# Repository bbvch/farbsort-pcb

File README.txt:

Eagle design files for Farbsort Cape for Beagle Bone

My work was based on Adafruit's Proto Cape Kit for Beagle Bone. See details below.

Adafruit Proto Cape Kit for Beagle Bone

These are the Eagle CAD files for the Adafruit Proto Cape Kit for Beagle Bone:
  ----> http://www.adafruit.com/products/572

Adafruit invests time and resources providing this open source design, please support Adafruit and open-source hardware by purchasing products from Adafruit!

Add some circuitry to your Beagle Bone with our lovely Proto Cape. If you have a 'Bone you need one of these! This PCB fits neatly on top of a Beagle Bone, without getting in the way of the Ethernet jack, and provides a breakout to both 46 pin headers - with individual numbering to keep them straight. We also threw down some strips to access the 5V and 3V power supplies as well as two SMT breakouts, one for SOIC-8's and one for SOT-23's.

Kit comes with a double-sided FR4 PCB and 3 sticks of header. You'll need to place the header into the Beagle Bone and then solder the Proto Cape PCB in place, but its very easy and should take only 10 minutes max even for beginners

All text above must be included in any redistribution

Designed by Limor Fried/Ladyada and Kevin Townsend for Adafruit Industries.
Creative Commons Attribution/Share-Alike, all text above must be included in any redistribution

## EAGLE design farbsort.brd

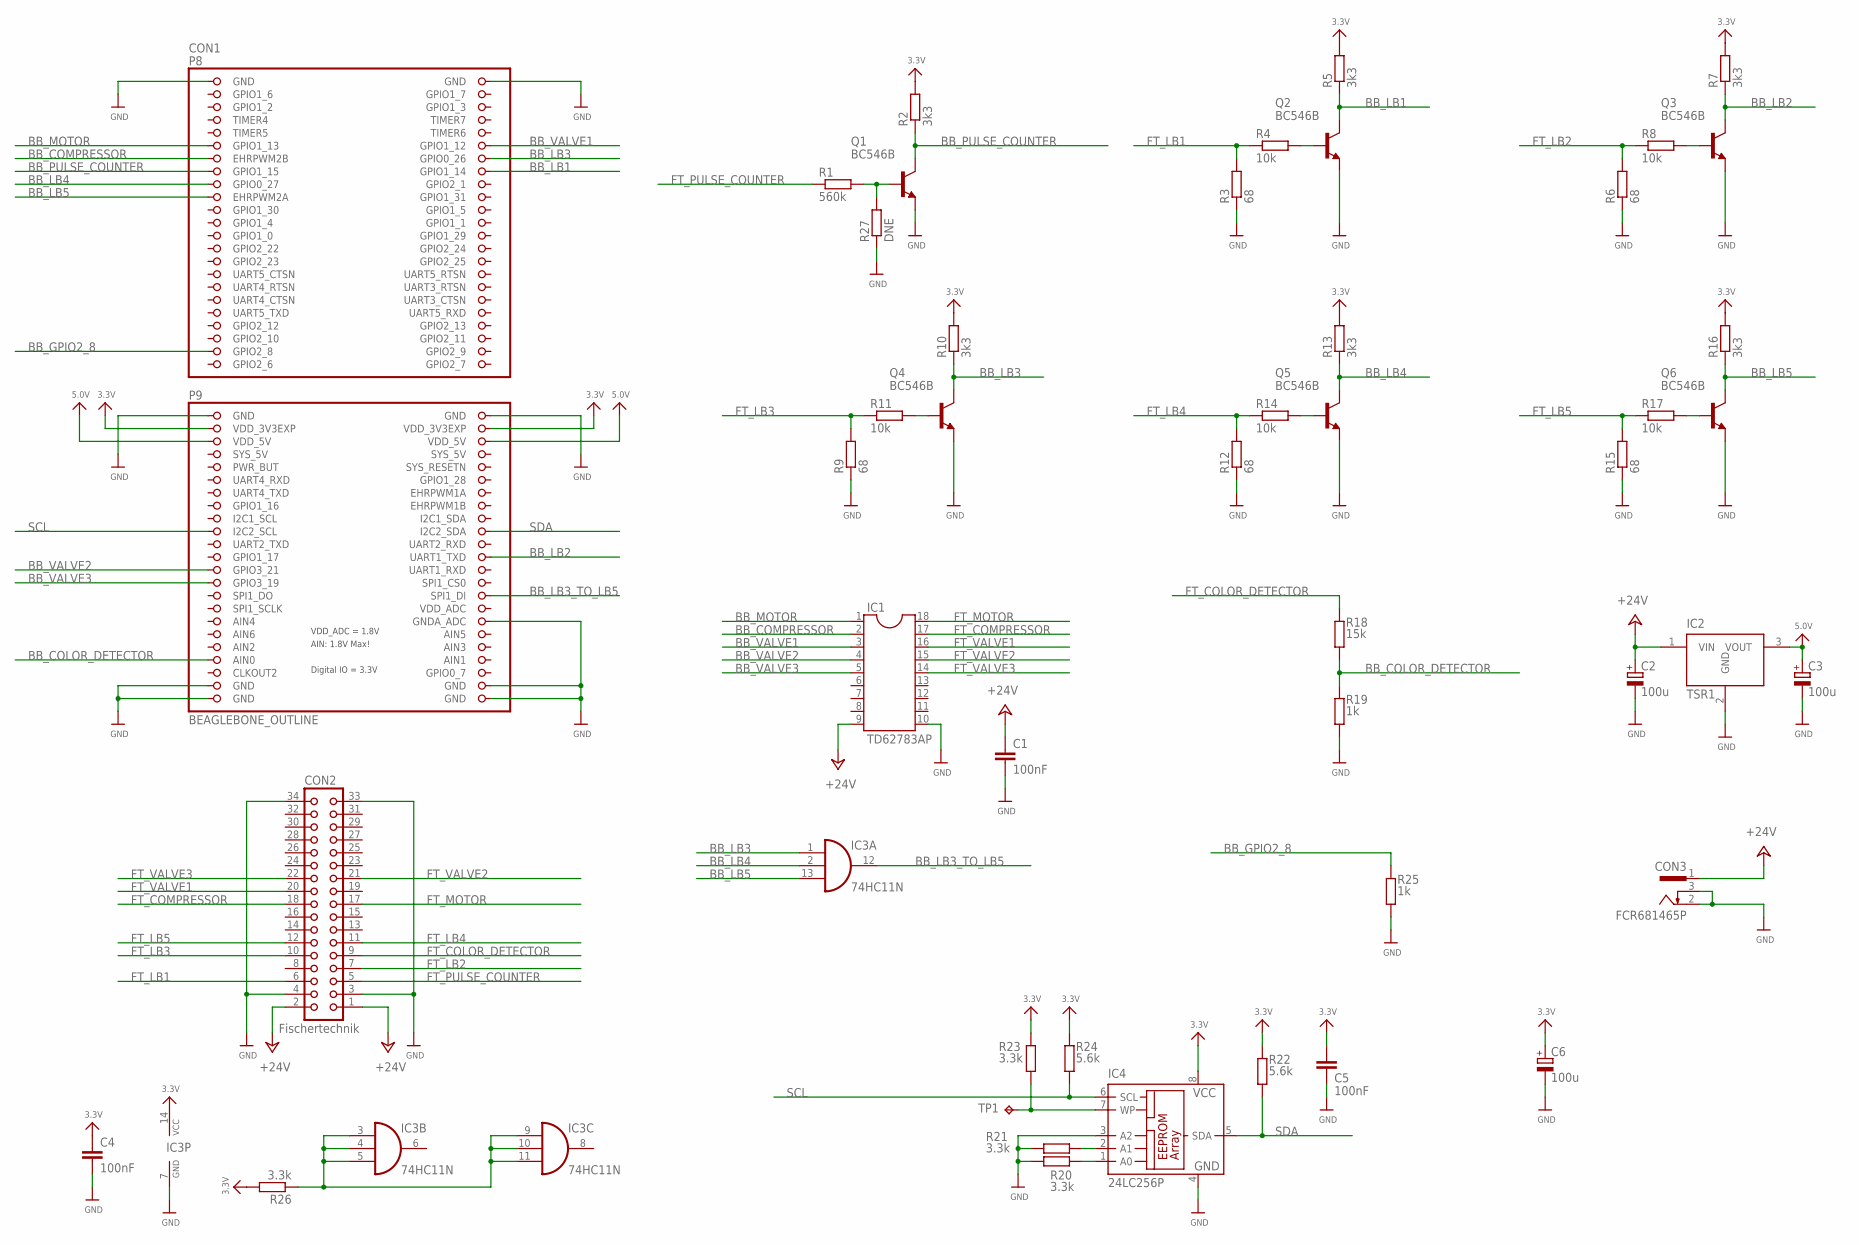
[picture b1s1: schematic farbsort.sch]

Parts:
C1, C4, C5: 100nF; C025-024X044
C2, C3, C6: 100u; B45181B
CON1: BEAGLEBONE_OUTLINE; BEAGLEBONE_SHIELD
CON2: Fischertechnik; CON34
CON3: FCR681465P; SCD-014-A
IC1: TD62783AP; DIL18
IC2: TSR1
IC3: 74HC11N; DIL14
IC4: 24LC256P; DIL8
Q1, Q2, Q3, Q4, Q5, Q6: BC546B; TO92-EBC
R1: 560k; 0204V
R2, R5, R7, R10, R13, R16: 3k3; 0204V
R3, R6, R9, R12, R15: 68; 0204V
R4, R8, R11, R14, R17: 10k; 0204V
R18: 15k; 0204V
R19, R25: 1k; 0204V
R20, R21, R23, R26: 3.3k; 0204V
R22, R24: 5.6k; 0204V
R27: DNE; 0204V
TP1: TPB1,27; B1,27

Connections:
3.3V: C4.1, C5.1, C6.+, CON1.49 (VDD_3V3EXP), CON1.50 (VDD_3V3EXP), IC3.14 (VCC), IC4.8 (VCC), R2.2, R5.2, R7.2, R10.2, R13.2, R16.2, R22.1, R23.1, R24.1, R26.2
5.0V: C3.+, CON1.51 (VDD_5V), CON1.52 (VDD_5V), IC2.3 (VOUT)
+24V: C1.1, C2.+, CON2.1, CON2.2, CON3.1, IC1.9, IC2.1 (VIN)
BB_COLOR_DETECTOR: CON1.85 (AIN0), R18.2, R19.1
BB_COMPRESSOR: CON1.13 (EHRPWM2B), IC1.2
BB_GPIO2_8: CON1.43 (GPIO2_8), R25.1
BB_LB1: CON1.16 (GPIO1_14), Q2.C, R5.1
BB_LB2: CON1.70 (UART1_TXD), Q3.C, R7.1
BB_LB3: CON1.14 (GPIO0_26), IC3.1 (I0), Q4.C, R10.1
BB_LB3_TO_LB5: CON1.76 (SPI1_DI), IC3.12 (O)
BB_LB4: CON1.17 (GPIO0_27), IC3.2 (I1), Q5.C, R13.1
BB_LB5: CON1.19 (EHRPWM2A), IC3.13 (I2), Q6.C, R16.1
BB_MOTOR: CON1.11 (GPIO1_13), IC1.1
BB_PULSE_COUNTER: CON1.15 (GPIO1_15), Q1.C, R2.1
BB_VALVE1: CON1.12 (GPIO1_12), IC1.3
BB_VALVE2: CON1.71 (GPIO3_21), IC1.4
BB_VALVE3: CON1.73 (GPIO3_19), IC1.5
FT_COLOR_DETECTOR: CON2.9, R18.1
FT_COMPRESSOR: CON2.18, IC1.17
FT_LB1: CON2.6, R3.2, R4.1
FT_LB2: CON2.7, R6.2, R8.1
FT_LB3: CON2.10, R9.2, R11.1
FT_LB4: CON2.11, R12.2, R14.1
FT_LB5: CON2.12, R15.2, R17.1
FT_MOTOR: CON2.17, IC1.18
FT_PULSE_COUNTER: CON2.5, R1.1
FT_VALVE1: CON2.20, IC1.16
FT_VALVE2: CON2.21, IC1.15
FT_VALVE3: CON2.22, IC1.14
GND: C1.2, C2.-, C3.-, C4.2, C5.2, C6.-, CON1.1 (GND), CON1.2 (GND), CON1.47 (GND), CON1.48 (GND), CON1.80 (GNDA_ADC), CON1.89 (GND), CON1.90 (GND), CON1.91 (GND), CON1.92 (GND), CON2.3, CON2.4, CON2.33, CON2.34, CON3.2, CON3.3, IC1.10, IC2.2 (GND), IC3.7 (GND), IC4.3 (A2), IC4.4 (GND), Q1.E, Q2.E, Q3.E, Q4.E, Q5.E, Q6.E, R3.1, R6.1, R9.1, R12.1, R15.1, R19.2, R20.1, R21.1, R25.2, R27.1
unnamed: Q1.B, R1.2, R27.2
unnamed: IC3.3 (I0), IC3.4 (I1), IC3.5 (I2), IC3.9 (I0), IC3.10 (I1), IC3.11 (I2), R26.1
unnamed: Q2.B, R4.2
unnamed: IC4.7 (WP), R23.2, TP1.TP
unnamed: Q3.B, R8.2
unnamed: IC4.2 (A1), R21.2
unnamed: IC4.1 (A0), R20.2
unnamed: Q4.B, R11.2
unnamed: Q5.B, R14.2
unnamed: Q6.B, R17.2
SCL: CON1.65 (I2C2_SCL), IC4.6 (SCL), R24.2
SDA: CON1.66 (I2C2_SDA), IC4.5 (SDA), R22.2
SYS_5V: CON1.53 (SYS_5V), CON1.54 (SYS_5V)
VDD_ADC: CON1.78 (VDD_ADC)

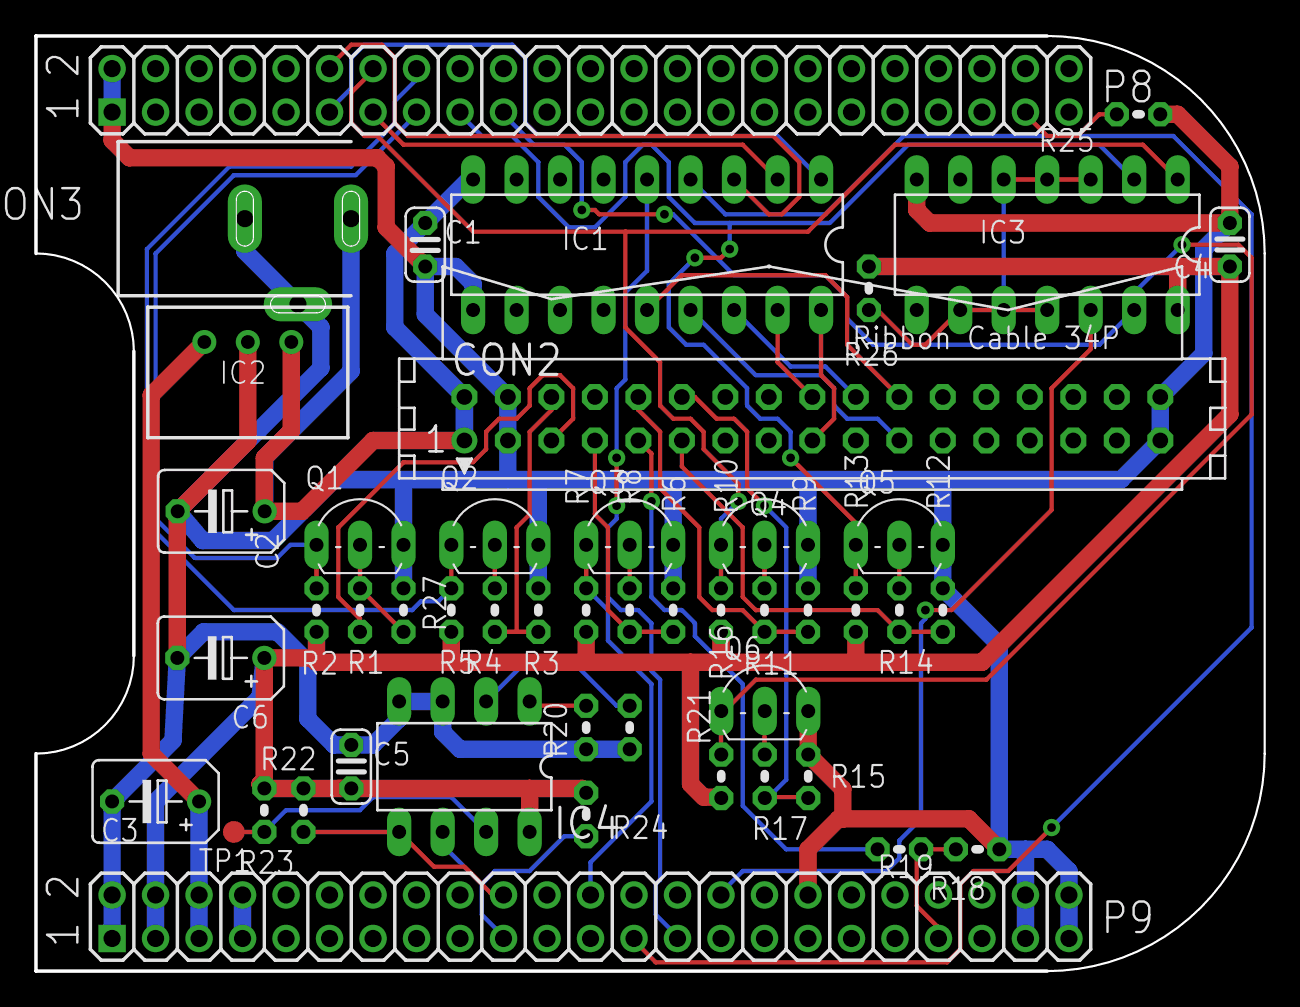
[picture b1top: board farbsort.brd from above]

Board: 2 copper layers, 71.7 x 54.6 mm, 47 parts (0 on the bottom side), 43 nets.

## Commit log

2016-10-27 add schematic and layout
2016-10-27 add README.txt
2016-10-27 add eagle project file
